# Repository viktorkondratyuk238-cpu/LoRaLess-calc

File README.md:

# LoRaLess calc

A handheld calculator built around an ESP32-C3. It has a keypad, a small OLED screen, and it passes messages to other calculators over ESP-NOW (the chip's built-in radio, not LoRa).

**Status:** the design and firmware are in progress. The firmware compiles and its logic tests pass on a PC. Nothing has run on the physical board yet. See [PROGRESS.md](PROGRESS.md) for what is done and what is still open.

## Contents

| Path | What it is |
|---|---|
| `lora-calculator_jlcpcb.kicad_sch` | KiCad schematic of the PCB |
| `bom_jlcpcb.csv` | Bill of materials for JLCPCB assembly |
| `firmware/src/` | Chip firmware: keypad, calculator, screen, messaging, ESP-NOW |
| `firmware/test*.cpp` | Logic tests that run on a PC, with no board needed |
| `firmware/stubs/` | Fake Arduino, Wire and MCP23017 headers so the tests run on a PC |
| `firmware/tools/check_board.py` | Checks the schematic wiring against what the firmware expects |
| `firmware/tools/netcheck.py` | Lists which pins connect to which nets in the schematic |
| `firmware/platformio.ini` | Board settings and one build target per calculator (`calc1` to `calc4`) |

## Hardware

- **MCU:** ESP32-C3-WROOM-02U module
- **Keypad:** 30 keys in a 6 × 5 matrix, read through an MCP23017 I/O expander at I2C address 0x20
- **Screen:** 1.54-inch 128 × 64 OLED with an SSD1317 controller, connected over I2C (header J2: GND, VCC, SCL, SDA)
- **Power:** USB-C input, MCP73831 battery charger, AP2112K-3.3 regulator, LiPo cable (J3)
- **Extra button:** SW31 is a power switch.

### Parts not in the PCB BOM

These are not in `bom_jlcpcb.csv` and must be sourced separately:

- **Screen:** 1.54-inch 128 × 64 OLED (SSD1317), I2C, connected to header J2 (GND, VCC, SCL, SDA).
- **Battery:** 500 mAh 1S LiPo (3.7 V nominal), connected to the LiPo cable header J3. The MCP73831 charger on the board charges it over USB-C.
- **Antenna:** 2.4 GHz T-style omnidirectional antenna, 40 mm version (the listing also has a 90 mm version), on a short coax pigtail with a small IPX1 / U.FL-type connector. It is sold for ELRS/TBS receivers. Connect it to the ESP32-C3-WROOM-02U module's external antenna pad (the "U" variant has a U.FL connector for this).

## Keys

Layout (row 1 at top, column 1 at left; from `KEYMAP` in `firmware/src/main.cpp`):

|| Col 1| Col 2 | Col 3 | Col 4 | Col 5 |
|---|---|---|---|---|---|
| Row 1 | C | DEL | +/- | MEMW | COMMA |
| Row 2 | x² | SQRT | ^ | MR | MC |
| Row 3 | 7 | 8 | 9 | COMP | F↔D |
| Row 4 | 4 | 5 | 6 | ( | ) |
| Row 5 | 1 | 2 | 3 | * | / |
| Row 6 | 0 | . | = | + | - |

**Calculator screen**

- `0`-`9`, `.`: type a number. Typing after a result starts a new calculation.
- `+ - * / ^`: add an operator. After a result, it chains from that result.
- `( )`: add a bracket.
- `=`: evaluate and show the result.
- `x²` / `SQRT`: square / square root of the last number or result.
- `C`: clear the calculation. `DEL`: delete the last digit typed, or the last token if no digits are typed.
- `+/-`: flip the sign of the number being typed, or of the last result.
- `COMP`: scale the last fraction by a whole number (type the number, then `=`).
- `F↔D`: toggle fraction / decimal display (only after an exact result).
- `MEMW`: store the number being typed, or the last result, in memory. `MR`: recall memory (only if set). `MC`: clear memory.
- `COMMA`: open the contacts screen.

**Contacts screen**

- `( )`: move the selection up / down.
- `=`: open the selected chat.
- `COMMA`: back to the calculator.

**Chat screen**

- `0`-`9`: multi-tap letters. Press the same key again within 1 second to cycle its letters (1: `1 . , ? !`; 2: `2 A B C`; ... 9: `9 W X Y Z`; 0: `0` and space). Press a different key, or wait over 1 second, for the next letter.
- `. + - * / ^`: type that symbol.
- `x²` / `SQRT`: replace the last number in the message with its square / square root.
- `COMP`: start a COMP scale on the last fraction; type a whole number, then `=`.
- `F↔D`: toggle fraction / decimal display.
- `=`: press twice within 0.5 s to send. One press types an `=`.
- `DEL`: delete the last character. `C`: clear the message.
- `( )`: scroll the chat up / down (any other key returns to the bottom).
- `COMMA`: leave the chat, back to the calculator.
- Messages are up to 120 characters.

## Building the firmware

The firmware uses [PlatformIO](https://platformio.org/). From the `firmware` folder:

```
pio run -e calc1          # build for calculator 1 (calc1 to calc4 are the four boards)
pio run -e calc1 -t upload
```

The platform is pinned to `espressif32@6.9.0` and the USB serial flags are set in `platformio.ini`. The newest platform fails to build this code.

## Running the tests

The tests compile on a PC with g++ (C++17). From the `firmware` folder, run every test for each board (DEVICE_ID 1 to 4):

```
bash run_tests.sh
```

It prints one line per test and exits non-zero if any test fails. To run one test by hand, for example for board 1:

```
g++ -std=c++17 -DDEVICE_ID=1 -Istubs -Isrc -o test_comm test_comm.cpp && ./test_comm
```

## Checking the schematic

Run the wiring checks from the repo root (Python 3):

```
python firmware/tools/check_board.py lora-calculator_jlcpcb.kicad_sch
```

It prints PASS or FAIL for each check and exits with a non-zero code if any fail. These checks confirm the wiring matches the firmware. They can't show that the screen, keys or radio work on a real board.

## Open items

- The screen is untested. The firmware has its own SSD1317 128 × 64 driver (`firmware/src/ssd1317_128x64.h`). The init sequence comes from the datasheet command table, not a vendor sample.
- The ESP-NOW radio code and the keypad have not run on hardware.
- The screen connector J2 and the LiPo cable J3 are not in the BOM (see [Parts not in the PCB BOM](#parts-not-in-the-pcb-bom)).

Full list: [PROGRESS.md](PROGRESS.md).
Images:

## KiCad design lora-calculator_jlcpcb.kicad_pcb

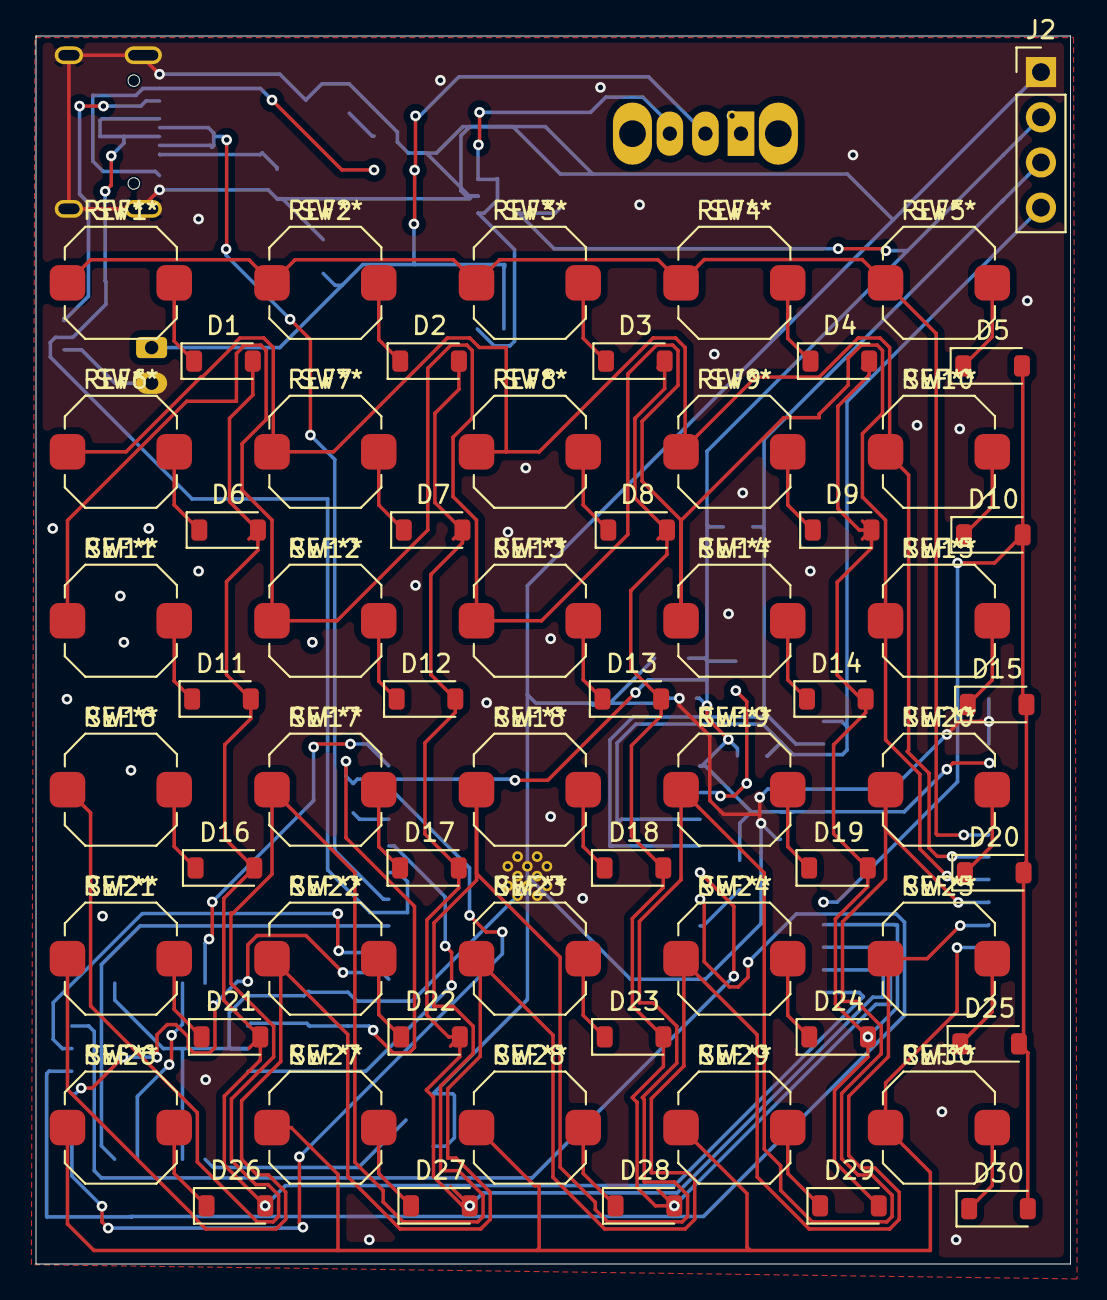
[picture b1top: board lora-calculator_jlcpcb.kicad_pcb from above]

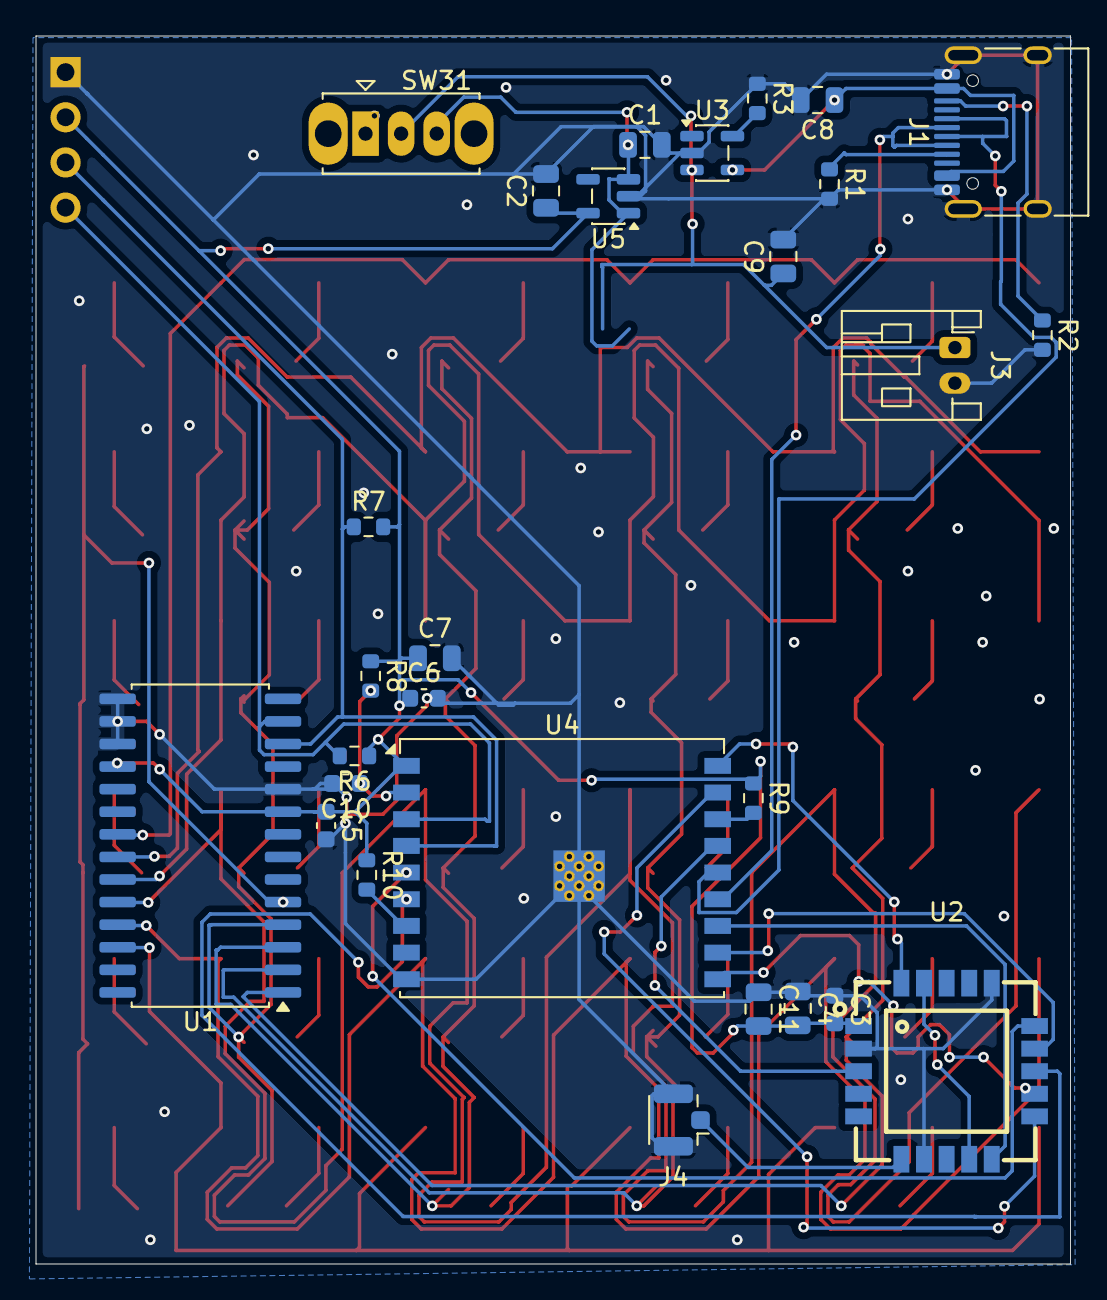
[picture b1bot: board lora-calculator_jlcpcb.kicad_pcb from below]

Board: 2 copper layers, 58.2 x 69.1 mm, 89 parts (28 on the bottom side), 60 nets.

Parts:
C1, C2: 10 microfarad; C_0805_2012Metric
C3: 100 nF; C_0603_1608Metric
C4: 10 µF; C_0805_2012Metric
C5, C6: 100nF; C_0603_1608Metric
C7: 10uF; C_0805_2012Metric
C8, C9: 4.7uF; C_0805_2012Metric
C10: 1uF; C_0603_1608Metric
C11: 22 µF; C_0805_2012Metric
D1, D2, D3, D4, D5, D6, D7, D8, D9, D10, D11, D12, D13, D14, D15, D16, D17, D18, D19, D20, D21, D22, D23, D24, D25, D26, D27, D28, D29, D30: 1N4148; D_SOD-123
J1: USB-C; USB_C_Receptacle_HRO_TYPE-C-31-M-12
J2: PinHeader_1x04_P2.54mm_Vertical
J3: LipoCable; JST_PH_S2B-PH-K_1x02_P2.00mm_Horizontal
J4: Conn_Coaxial; U.FL_Hirose_U.FL-R-SMT-1_Vertical
R1, R2: 5,1k; R_0603_1608Metric
R3: 2k; R_0603_1608Metric
R6, R7: 4.7k; R_0603_1608Metric
R8, R9, R10: 10k; R_0603_1608Metric
SW1, SW2, SW3, SW4, SW5, SW6, SW7, SW8, SW9, SW10, SW11, SW12, SW13, SW14, SW15, SW16, SW17, SW18, SW19, SW20, SW21, SW22, SW23, SW24, SW25, SW26, SW27, SW28, SW29, SW30: SW_Push; SW_Push_1TS009xxxx-xxxx-xxxx_6x6x5mm
SW31: SW_SPDT; SW_Slide_SPDT_Straight_CK_OS102011MS2Q
U1: MCP23017x-x-SO; SOIC-28W_7.5x17.9mm_P1.27mm
U2: E22-900MM22S; WIRELM-SMD_20P-L10.0-W10.0-P1.27-TL
U3: MCP73831-2-OT; SOT-23-5
U4: ESP32-C3-WROOM-02U
U5: AP2112K-3.3; SOT-23-5

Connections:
+3.3V: C2.1, C3.2, C4.2, C5.1, C6.1, C7.1, C11.2, J2.2, R6.1, R7.2, R8.1, R9.1, R10.1, U1.9 (V_{DD}), U1.18 (~RESET), U2.1 (VCC), U4.1 (3V3), U5.5 (VOUT)
/COL_0: D1.2 (A), D6.2 (A), D11.2 (A), D16.2 (A), D21.2 (A), D26.2 (A), U1.1 (GPB0)
/COL_1: D2.2 (A), D7.2 (A), D12.2 (A), D17.2 (A), D22.2 (A), D27.2 (A), U1.2 (GPB1)
/COL_2: D3.2 (A), D8.2 (A), D13.2 (A), D18.2 (A), D23.2 (A), D28.2 (A), U1.3 (GPB2)
/COL_3: D4.2 (A), D9.2 (A), D14.2 (A), D19.2 (A), D24.2 (A), D29.2 (A), U1.4 (GPB3)
/COL_4: D5.2 (A), D10.2 (A), D15.2 (A), D20.2 (A), D25.2 (A), D30.2 (A), U1.5 (GPB4)
/D+: J1.A6 (D+), J1.B6 (D+), U4.14 (IO19)
/D-: J1.A7 (D-), J1.B7 (D-), U4.13 (IO18)
/ROW_0: SW1.1, SW2.1, SW3.1, SW4.1, SW5.1, U1.21 (GPA0)
/ROW_1: SW6.1, SW7.1, SW8.1, SW9.1, SW10.1, U1.22 (GPA1)
/ROW_2: SW11.1, SW12.1, SW13.1, SW14.1, SW15.1, U1.23 (GPA2)
/ROW_3: SW16.1, SW17.1, SW18.1, SW19.1, SW20.1, U1.24 (GPA3)
/ROW_4: SW21.1, SW22.1, SW23.1, SW24.1, SW25.1, U1.25 (GPA4)
/ROW_5: SW26.1, SW27.1, SW28.1, SW29.1, SW30.1, U1.26 (GPA5)
GND: C1.2, C2.2, C3.1, C4.1, C5.2, C6.2, C7.2, C8.2, C9.2, C10.2, C11.1, J1.A1 (GND), J1.A12 (GND), J1.B1 (GND), J1.B12 (GND), J1.SH (SHIELD), J2.1, J3.2, J4.2 (Ext), R1.2, R2.2, R3.1, U1.10 (V_{SS}), U1.15 (A0), U1.16 (A1), U1.17 (A2), U2.2 (GND), U2.7 (GND), U2.16 (GND), U3.2 (V_{SS}), U4.9 (GND), U4.19 (GND), U5.2 (GND)
unnamed: D1.1 (K), SW1.2
unnamed: D2.1 (K), SW2.2
unnamed: D3.1 (K), SW3.2
unnamed: D4.1 (K), SW4.2
unnamed: D5.1 (K), SW5.2
unnamed: D6.1 (K), SW6.2
unnamed: D7.1 (K), SW7.2
unnamed: D8.1 (K), SW8.2
unnamed: D9.1 (K), SW9.2
unnamed: D10.1 (K), SW10.2
unnamed: D11.1 (K), SW11.2
unnamed: D12.1 (K), SW12.2
unnamed: D13.1 (K), SW13.2
unnamed: D14.1 (K), SW14.2
unnamed: D15.1 (K), SW15.2
unnamed: D16.1 (K), SW16.2
unnamed: D17.1 (K), SW17.2
unnamed: D18.1 (K), SW18.2
unnamed: D19.1 (K), SW19.2
unnamed: D20.1 (K), SW20.2
unnamed: D21.1 (K), SW21.2
unnamed: D22.1 (K), SW22.2
unnamed: D23.1 (K), SW23.2
unnamed: D24.1 (K), SW24.2
unnamed: D25.1 (K), SW25.2
unnamed: D26.1 (K), SW26.2
unnamed: D27.1 (K), SW27.2
unnamed: D28.1 (K), SW28.2
unnamed: D29.1 (K), SW29.2
unnamed: D30.1 (K), SW30.2
unnamed: J1.A5 (CC1), R1.1
unnamed: J1.B5 (CC2), R2.1
unnamed: J2.3, R7.1, U1.12 (SCK), U4.4 (IO5)
unnamed: J2.4, R6.2, U1.13 (SDA), U4.3 (IO4)
unnamed: C9.1, J3.1, SW31.2 (B), U3.3 (V_{BAT})
unnamed: J4.1 (In), U2.6 (ANT)
unnamed: C1.1, SW31.3 (C), U5.1 (VIN), U5.3 (EN)
unnamed: U2.9 (TXEN), U2.19 (DIO2)
unnamed: U2.3 (NRST), U4.15 (IO3)
unnamed: U2.10 (RXEN), U4.12 (IO21/TXD)
unnamed: R3.2, U3.5 (PROG)
unnamed: C8.1, J1.A4 (VBUS), J1.A9 (VBUS), J1.B4 (VBUS), J1.B9 (VBUS), U3.4 (V_{DD})
unnamed: C10.1, R8.2, U4.2 (EN)
unnamed: R9.2, U4.16 (IO2)
unnamed: R10.2, U4.7 (IO8)

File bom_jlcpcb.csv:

Comment,Designator,Footprint,LCSC Part #
10 microfarad,"C1,C2",Capacitor_SMD:C_0805_2012Metric,C15850
100nF,"C5,C6",Capacitor_SMD:C_0603_1608Metric,C14663
10uF,C7,Capacitor_SMD:C_0805_2012Metric,C15850
4.7uF,"C8,C9",Capacitor_SMD:C_0805_2012Metric,C1779
1uF,C10,Capacitor_SMD:C_0603_1608Metric,C15849
1N4148,"D1,D2,D3,D4,D5,D6,D7,D8,D9,D10,D11,D12,D13,D14,D15,D16,D17,D18,D19,D20,D21,D22,D23,D24,D25,D26,D27,D28,D29,D30",Diode_SMD:D_SOD-123,C81598
USB-C,J1,Connector_USB:USB_C_Receptacle_HRO_TYPE-C-31-M-12,C165948
"5,1k","R1,R2",Resistor_SMD:R_0603_1608Metric,C23186
2k,R3,Resistor_SMD:R_0603_1608Metric,C22975
4.7k,"R6,R7",Resistor_SMD:R_0603_1608Metric,C23162
10k,"R8,R9,R10",Resistor_SMD:R_0603_1608Metric,C25804
SW_Push,"SW1,SW2,SW3,SW4,SW5,SW6,SW7,SW8,SW9,SW10,SW11,SW12,SW13,SW14,SW15,SW16,SW17,SW18,SW19,SW20,SW21,SW22,SW23,SW24,SW25,SW26,SW27,SW28,SW29,SW30",Button_Switch_SMD:SW_Push_1TS009xxxx-xxxx-xxxx_6x6x5mm,C412375
SW_SPDT,SW31,Button_Switch_SMD:SW_SPDT_Shouhan_MSK12C02,C431540
MCP23017x-x-SO,U1,Package_SO:SOIC-28W_7.5x17.9mm_P1.27mm,C47023
MCP73831-2-OT,U3,Package_TO_SOT_SMD:SOT-23-5,C424093
ESP32-C3-WROOM-02U,U4,RF_Module:ESP32-C3-WROOM-02U,C2926676
AP2112K-3.3,U5,Package_TO_SOT_SMD:SOT-23-5,C51118
